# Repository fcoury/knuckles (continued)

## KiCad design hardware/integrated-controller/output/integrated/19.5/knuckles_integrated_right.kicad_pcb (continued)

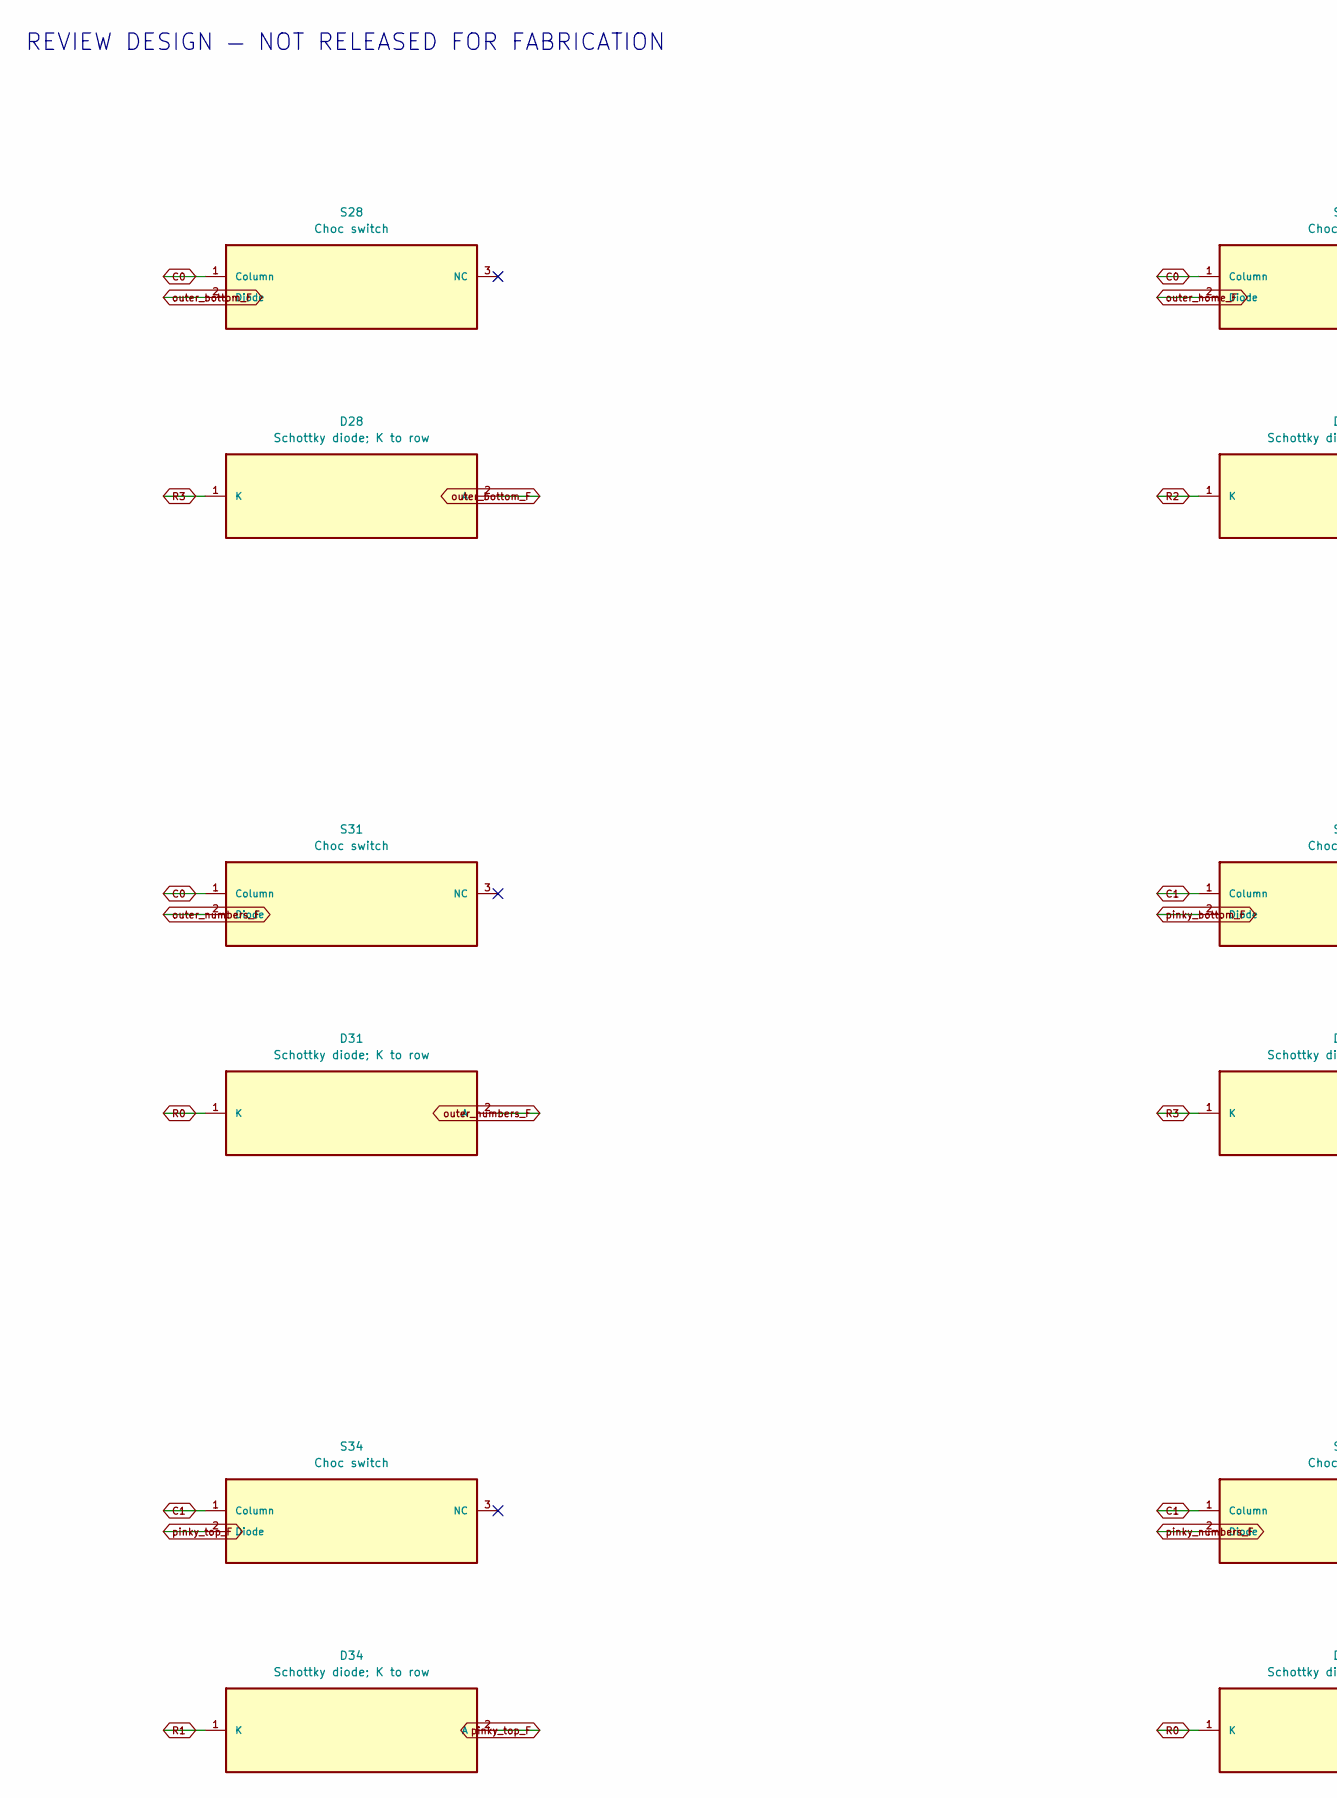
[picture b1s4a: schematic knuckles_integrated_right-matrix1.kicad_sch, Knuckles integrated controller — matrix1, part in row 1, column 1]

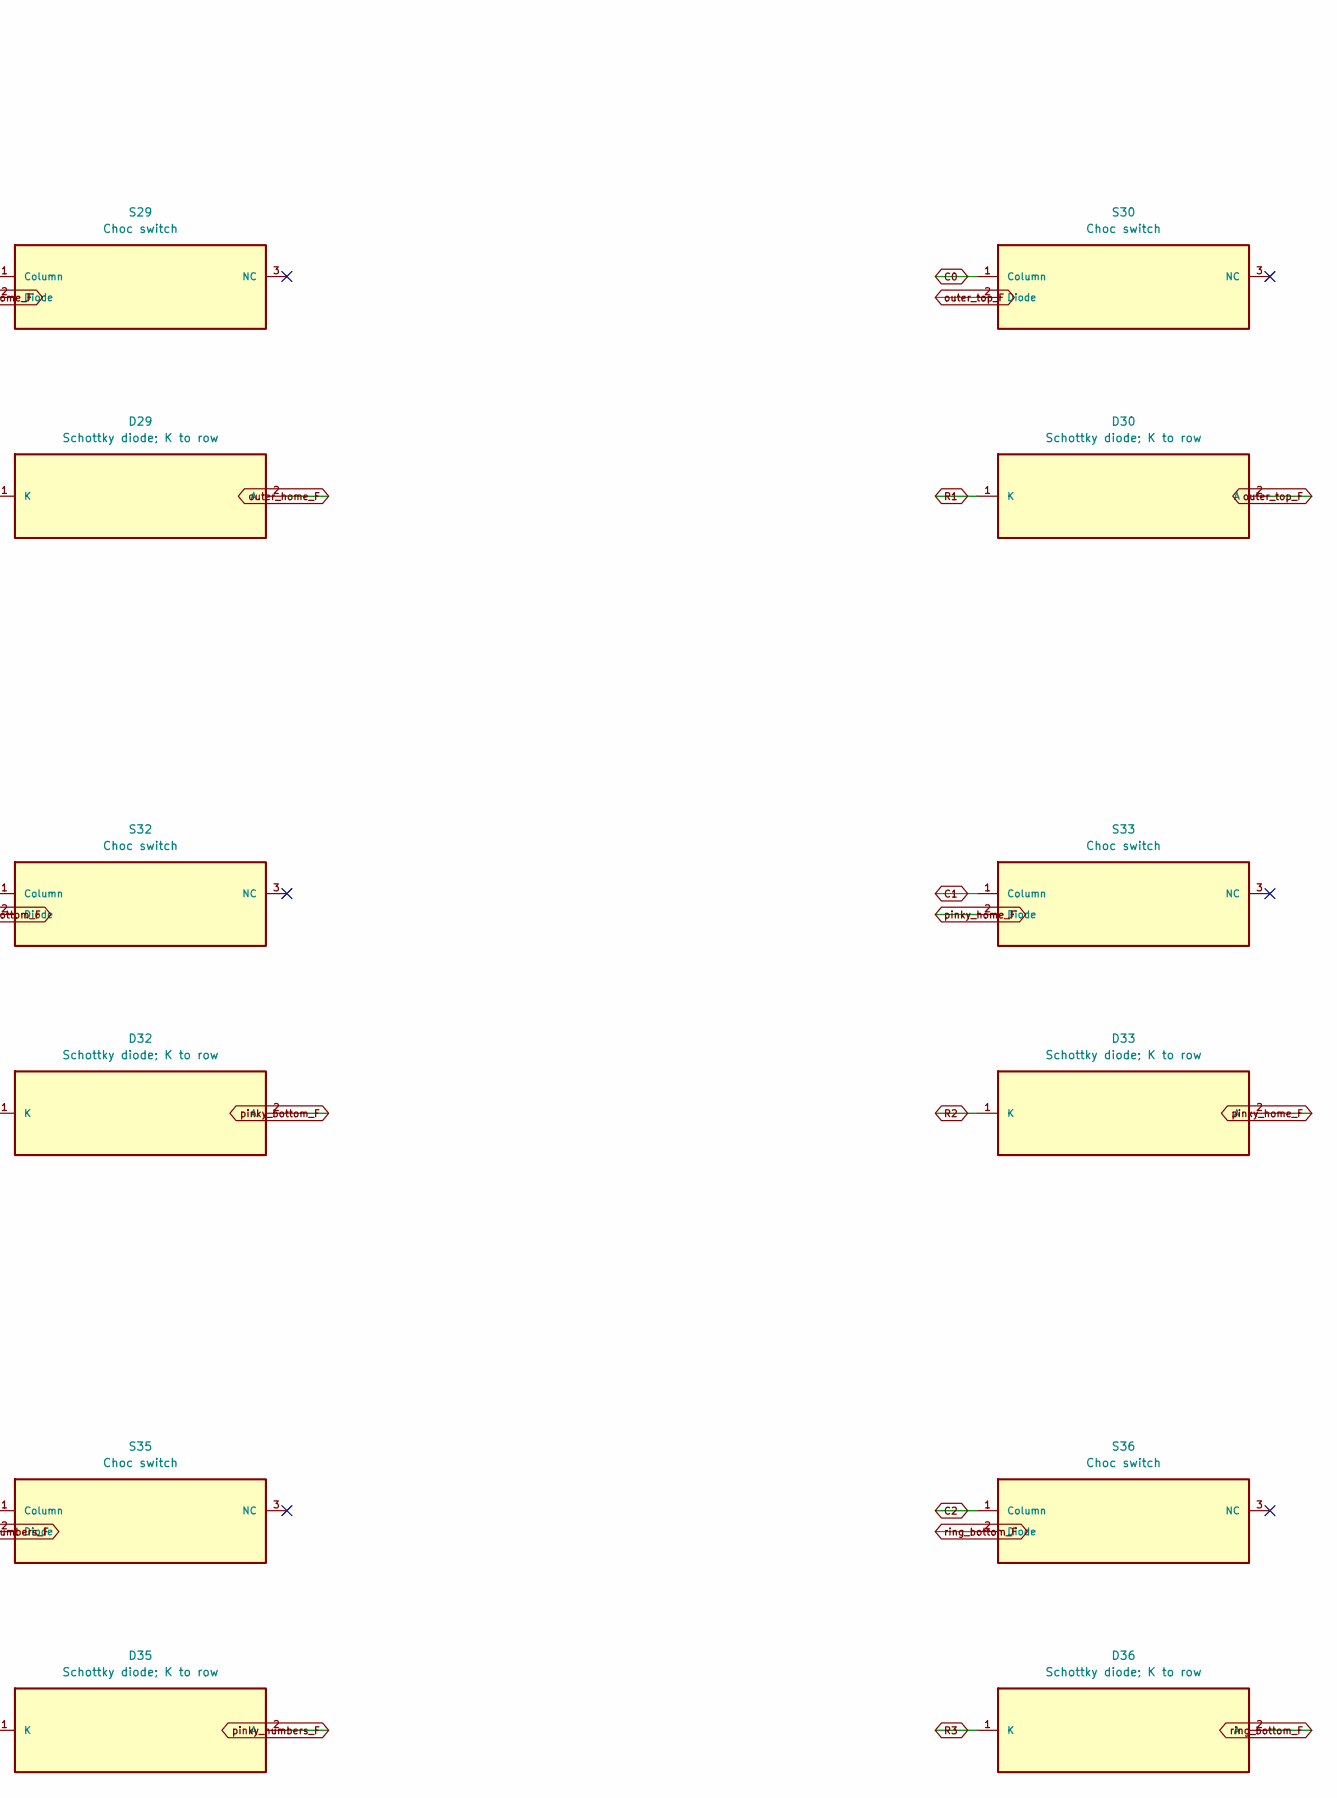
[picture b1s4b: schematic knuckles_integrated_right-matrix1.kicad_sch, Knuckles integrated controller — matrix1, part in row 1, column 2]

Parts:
D28, D29, D30, D31, D32, D33, D34, D35, D36: Schottky diode; K to row; diode_tht_sod123
S28, S29, S30, S31, S32, S33, S34, S35, S36: Choc switch; CPG1316S01D02

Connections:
C0: S28.1 (Column), S29.1 (Column), S30.1 (Column), S31.1 (Column); also elsewhere on the board
C1: S32.1 (Column), S33.1 (Column), S34.1 (Column), S35.1 (Column); also elsewhere on the board
C2: S36.1 (Column); also elsewhere on the board
R0: D31.1 (K), D35.1 (K); also elsewhere on the board
R1: D30.1 (K), D34.1 (K); also elsewhere on the board
R2: D29.1 (K), D33.1 (K); also elsewhere on the board
R3: D28.1 (K), D32.1 (K), D36.1 (K); also elsewhere on the board
outer_bottom_F: D28.2 (A), S28.2 (Diode)
outer_home_F: D29.2 (A), S29.2 (Diode)
outer_numbers_F: D31.2 (A), S31.2 (Diode)
outer_top_F: D30.2 (A), S30.2 (Diode)
pinky_bottom_F: D32.2 (A), S32.2 (Diode)
pinky_home_F: D33.2 (A), S33.2 (Diode)
pinky_numbers_F: D35.2 (A), S35.2 (Diode)
pinky_top_F: D34.2 (A), S34.2 (Diode)
ring_bottom_F: D36.2 (A), S36.2 (Diode)

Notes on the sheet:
REVIEW DESIGN — NOT RELEASED FOR FABRICATION

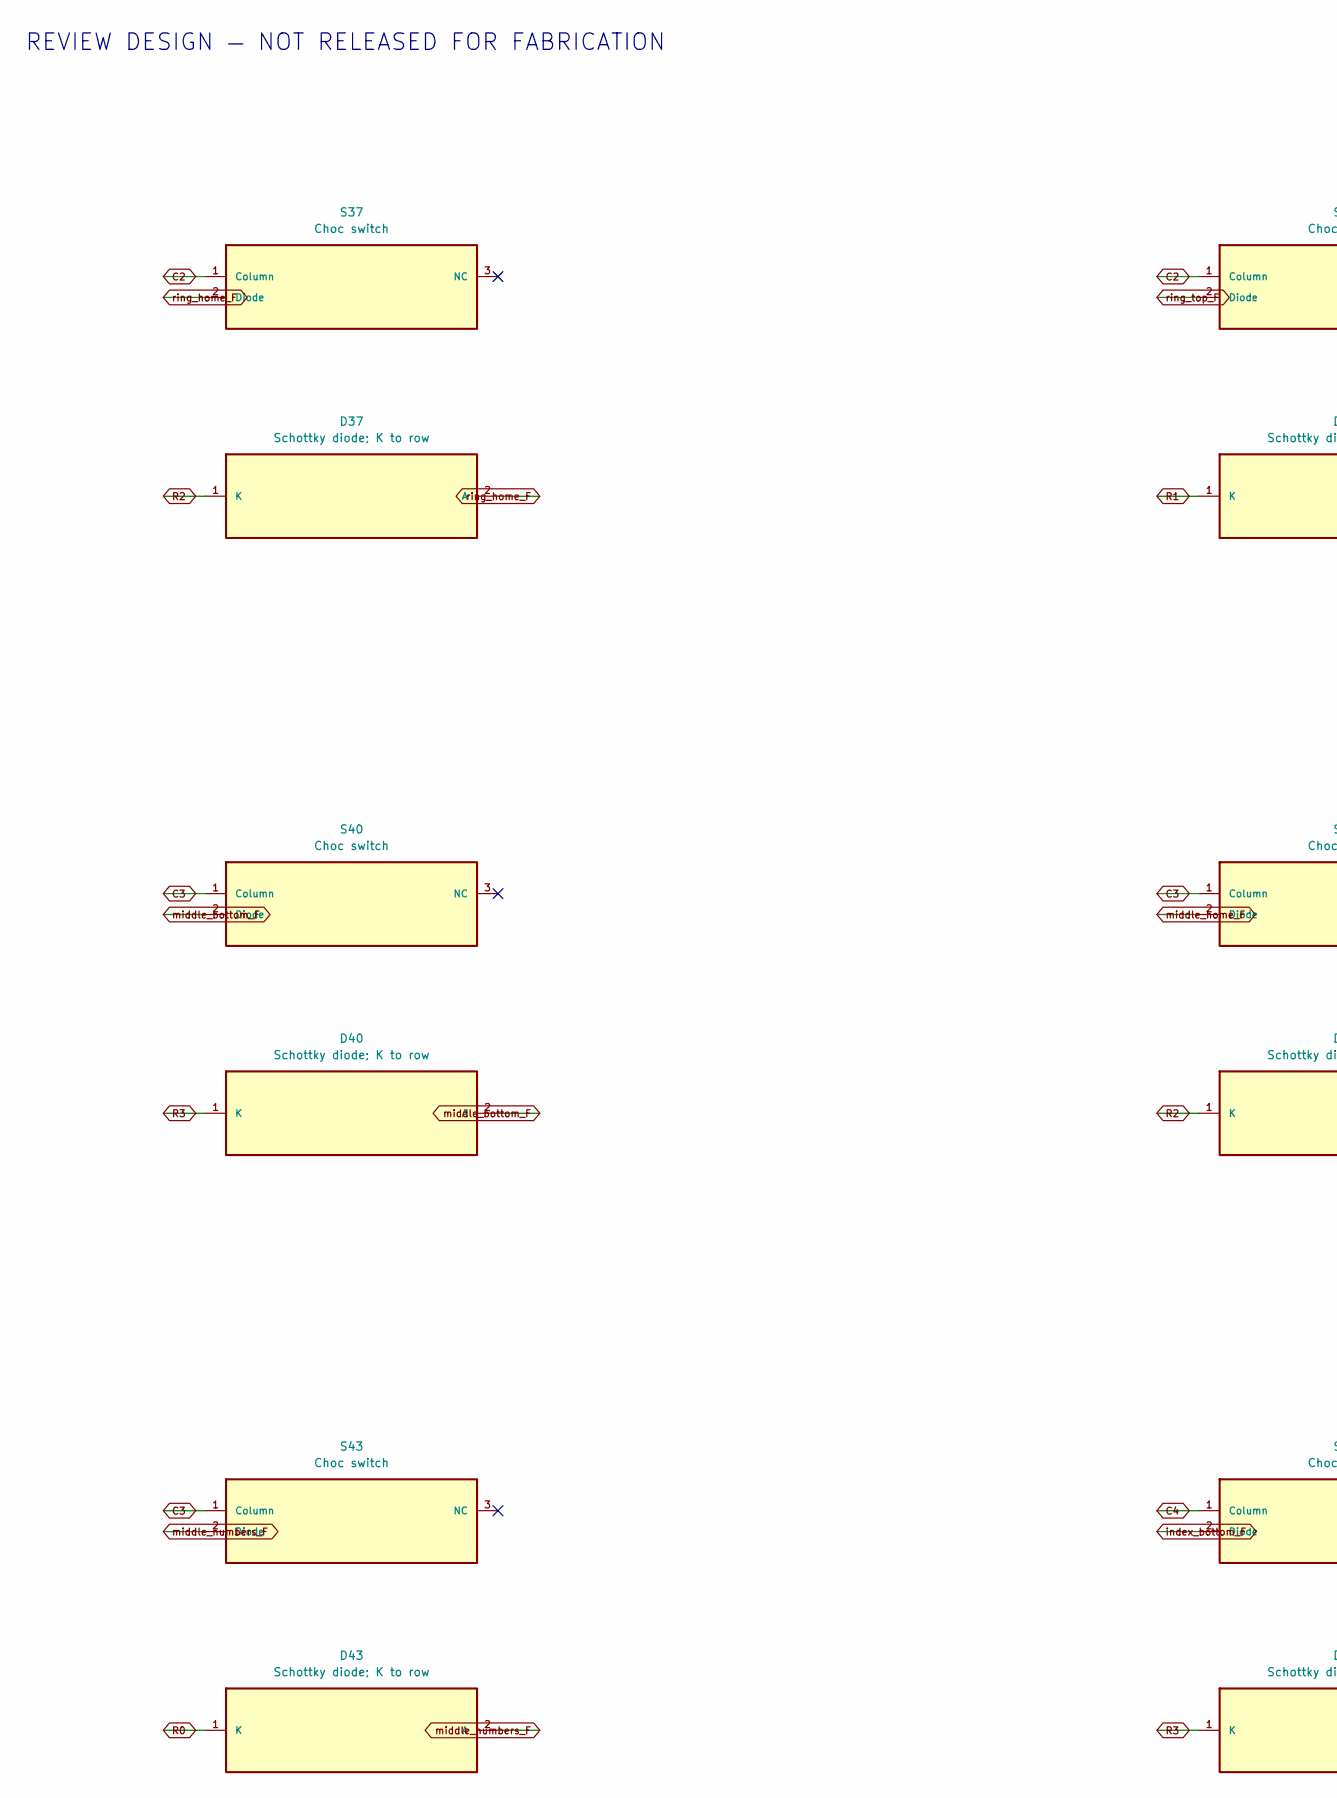
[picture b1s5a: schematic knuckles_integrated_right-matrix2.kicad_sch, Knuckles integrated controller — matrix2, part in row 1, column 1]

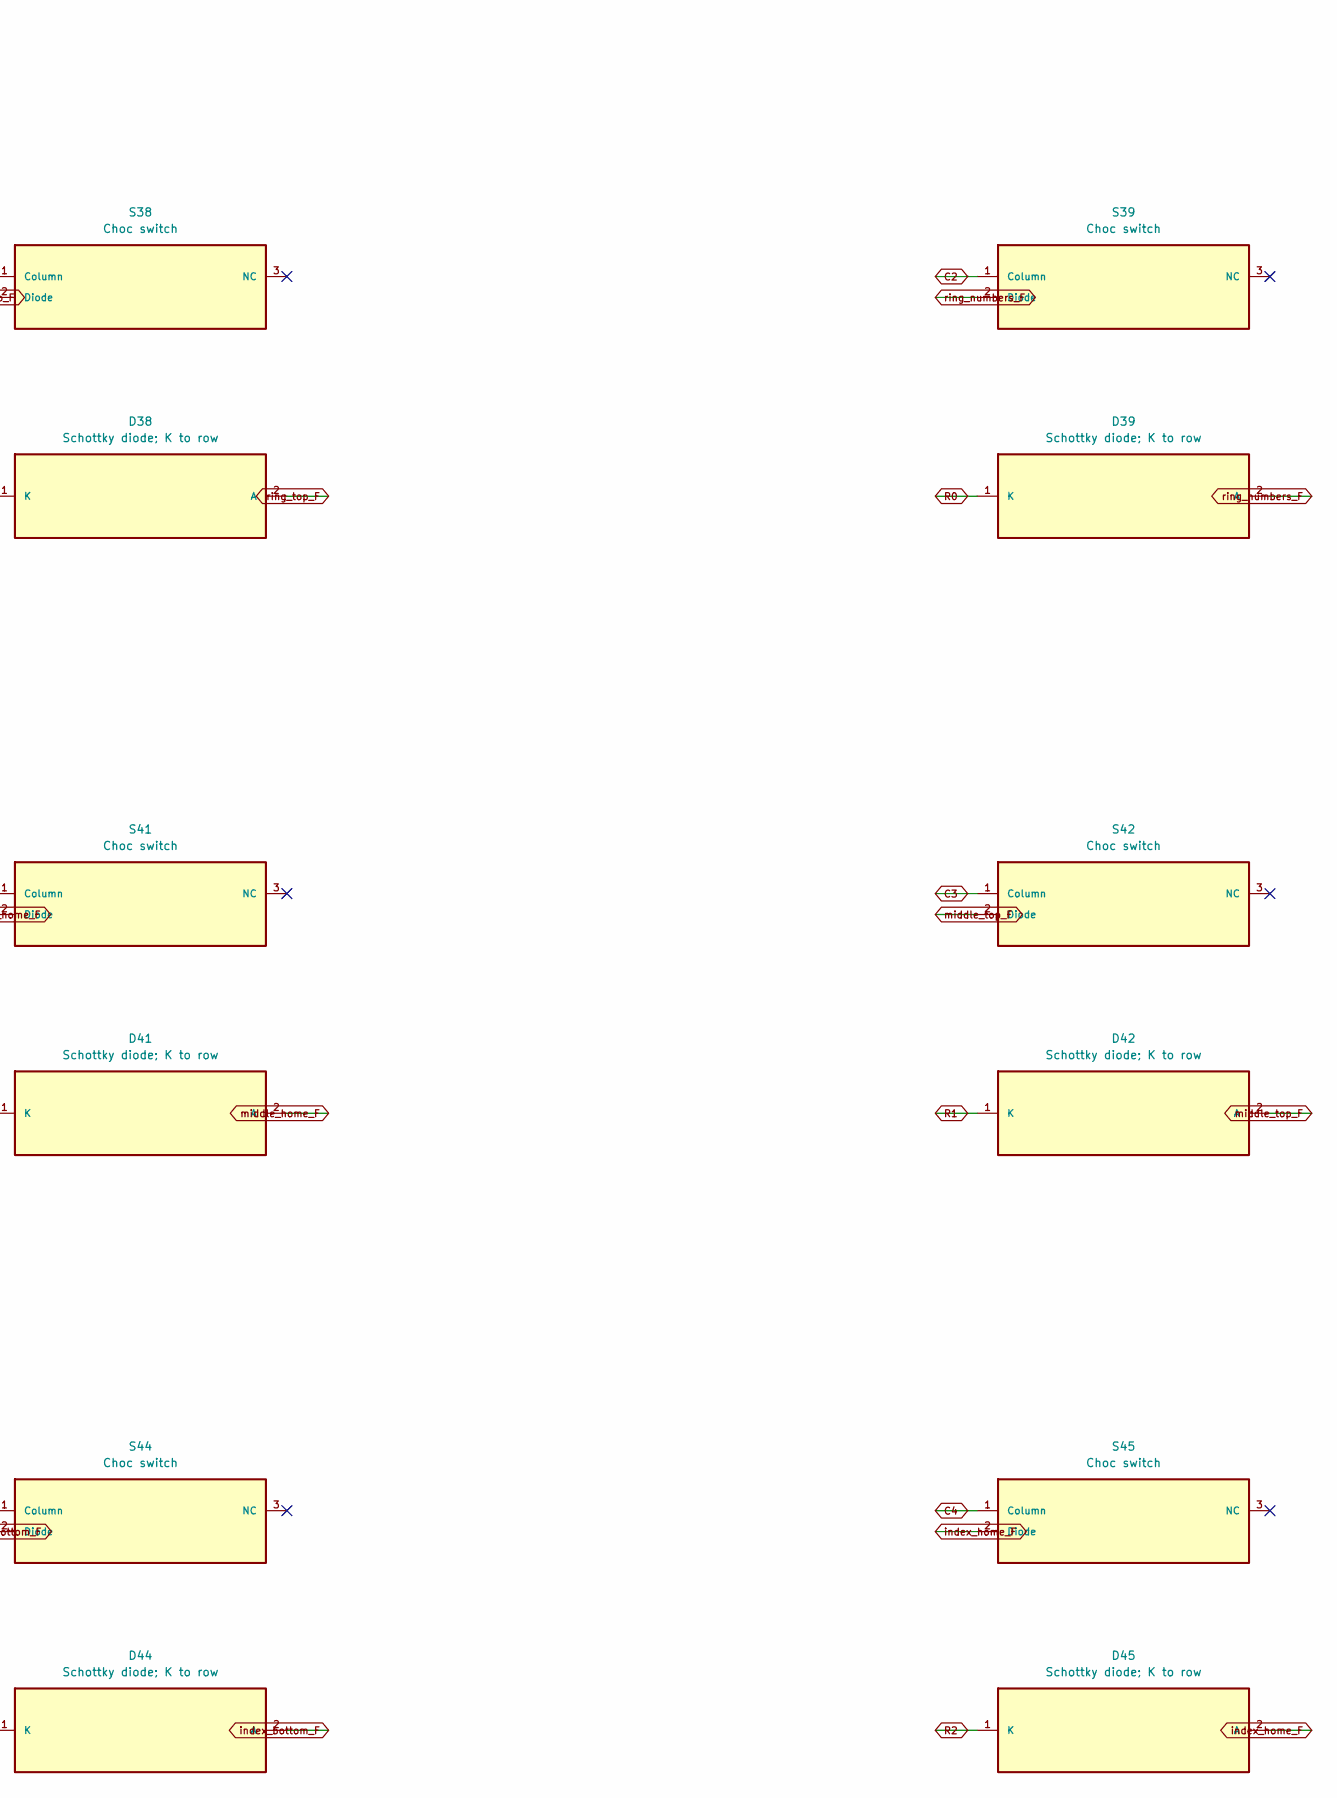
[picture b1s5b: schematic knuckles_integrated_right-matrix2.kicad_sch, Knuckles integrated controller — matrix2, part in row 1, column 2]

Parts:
D37, D38, D39, D40, D41, D42, D43, D44, D45: Schottky diode; K to row; diode_tht_sod123
S37, S38, S39, S40, S41, S42, S43, S44, S45: Choc switch; CPG1316S01D02

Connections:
C2: S37.1 (Column), S38.1 (Column), S39.1 (Column); also elsewhere on the board
C3: S40.1 (Column), S41.1 (Column), S42.1 (Column), S43.1 (Column); also elsewhere on the board
C4: S44.1 (Column), S45.1 (Column); also elsewhere on the board
R0: D39.1 (K), D43.1 (K); also elsewhere on the board
R1: D38.1 (K), D42.1 (K); also elsewhere on the board
R2: D37.1 (K), D41.1 (K), D45.1 (K); also elsewhere on the board
R3: D40.1 (K), D44.1 (K); also elsewhere on the board
index_bottom_F: D44.2 (A), S44.2 (Diode)
index_home_F: D45.2 (A), S45.2 (Diode)
middle_bottom_F: D40.2 (A), S40.2 (Diode)
middle_home_F: D41.2 (A), S41.2 (Diode)
middle_numbers_F: D43.2 (A), S43.2 (Diode)
middle_top_F: D42.2 (A), S42.2 (Diode)
ring_home_F: D37.2 (A), S37.2 (Diode)
ring_numbers_F: D39.2 (A), S39.2 (Diode)
ring_top_F: D38.2 (A), S38.2 (Diode)

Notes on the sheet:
REVIEW DESIGN — NOT RELEASED FOR FABRICATION

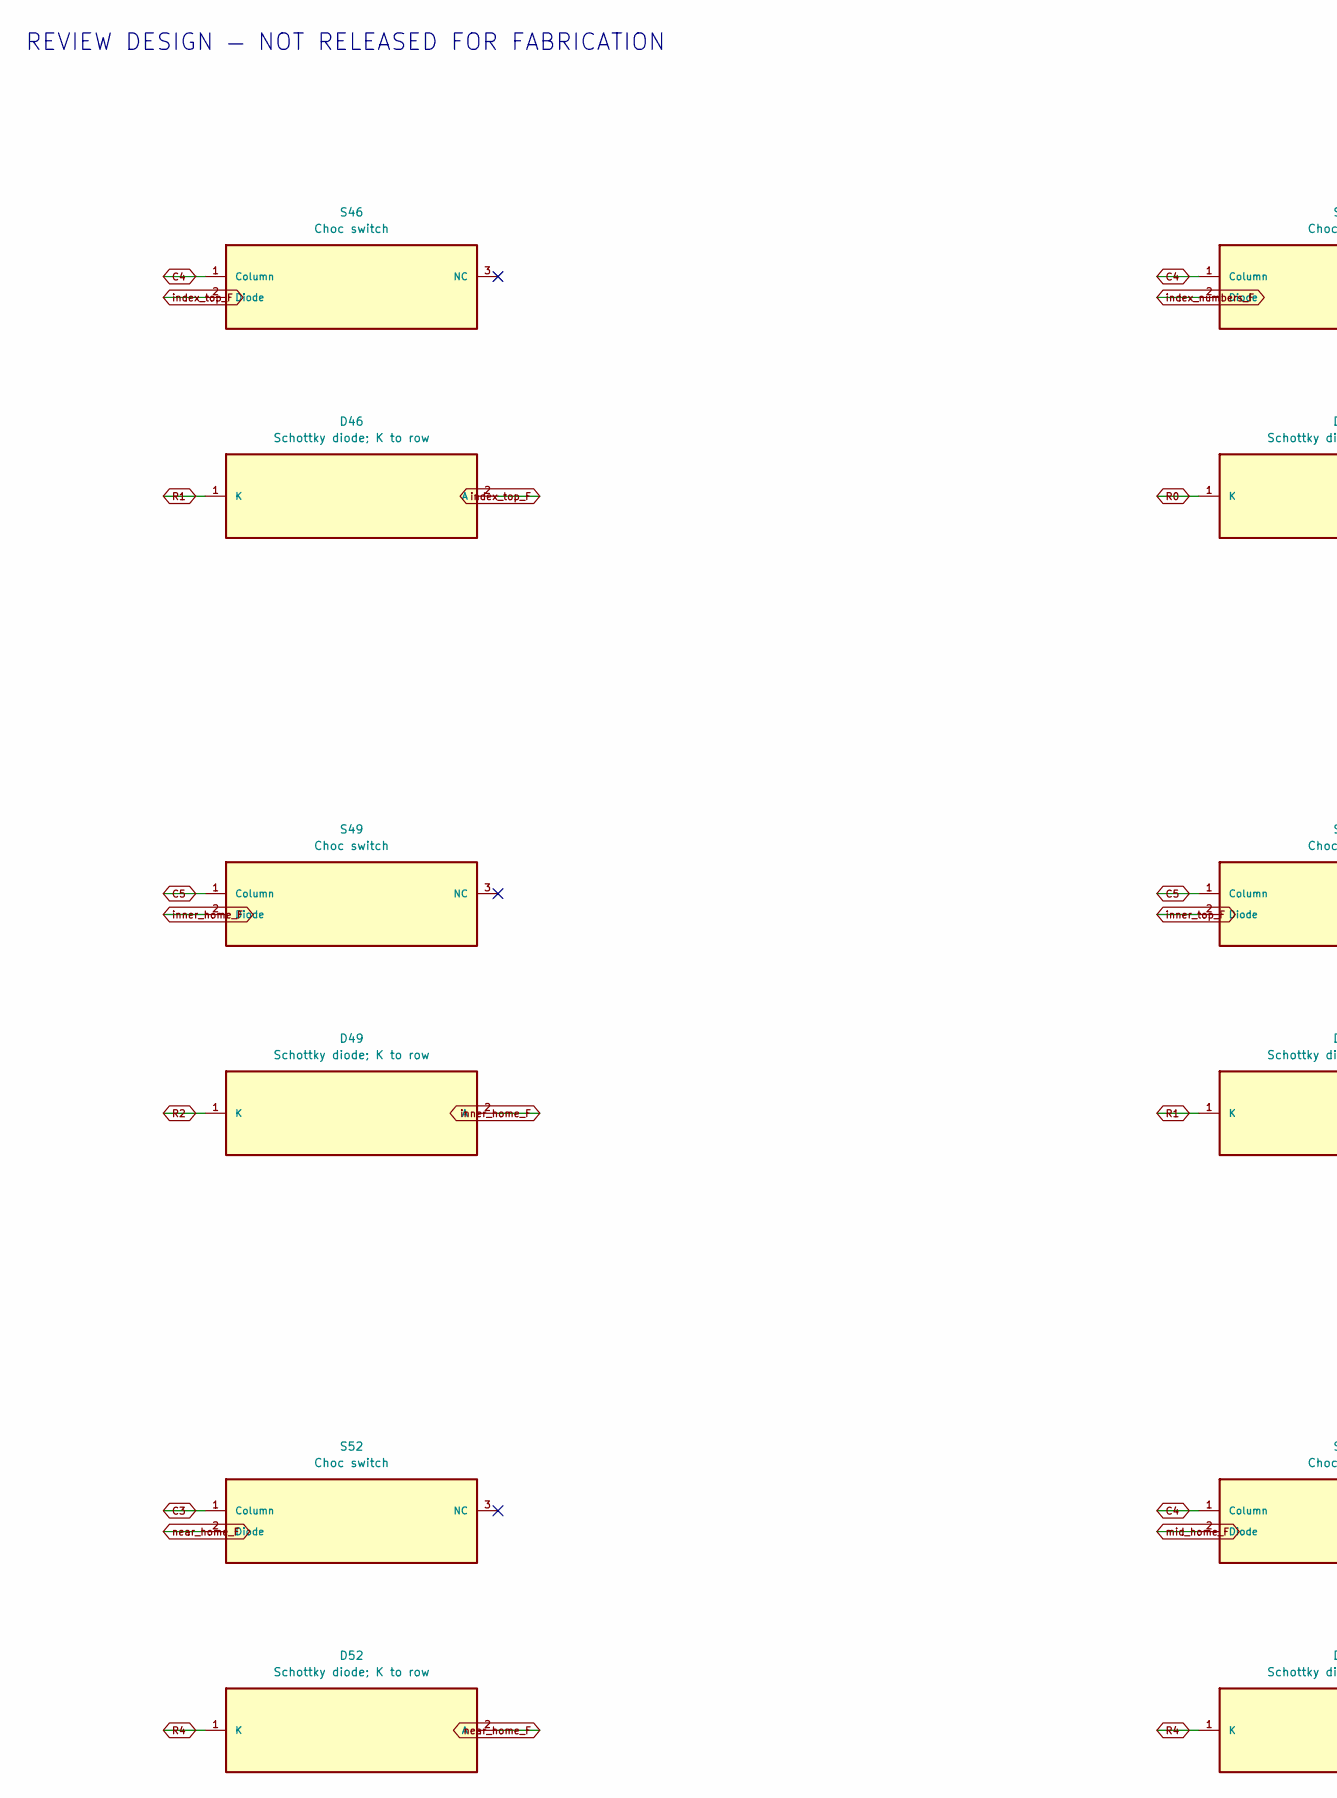
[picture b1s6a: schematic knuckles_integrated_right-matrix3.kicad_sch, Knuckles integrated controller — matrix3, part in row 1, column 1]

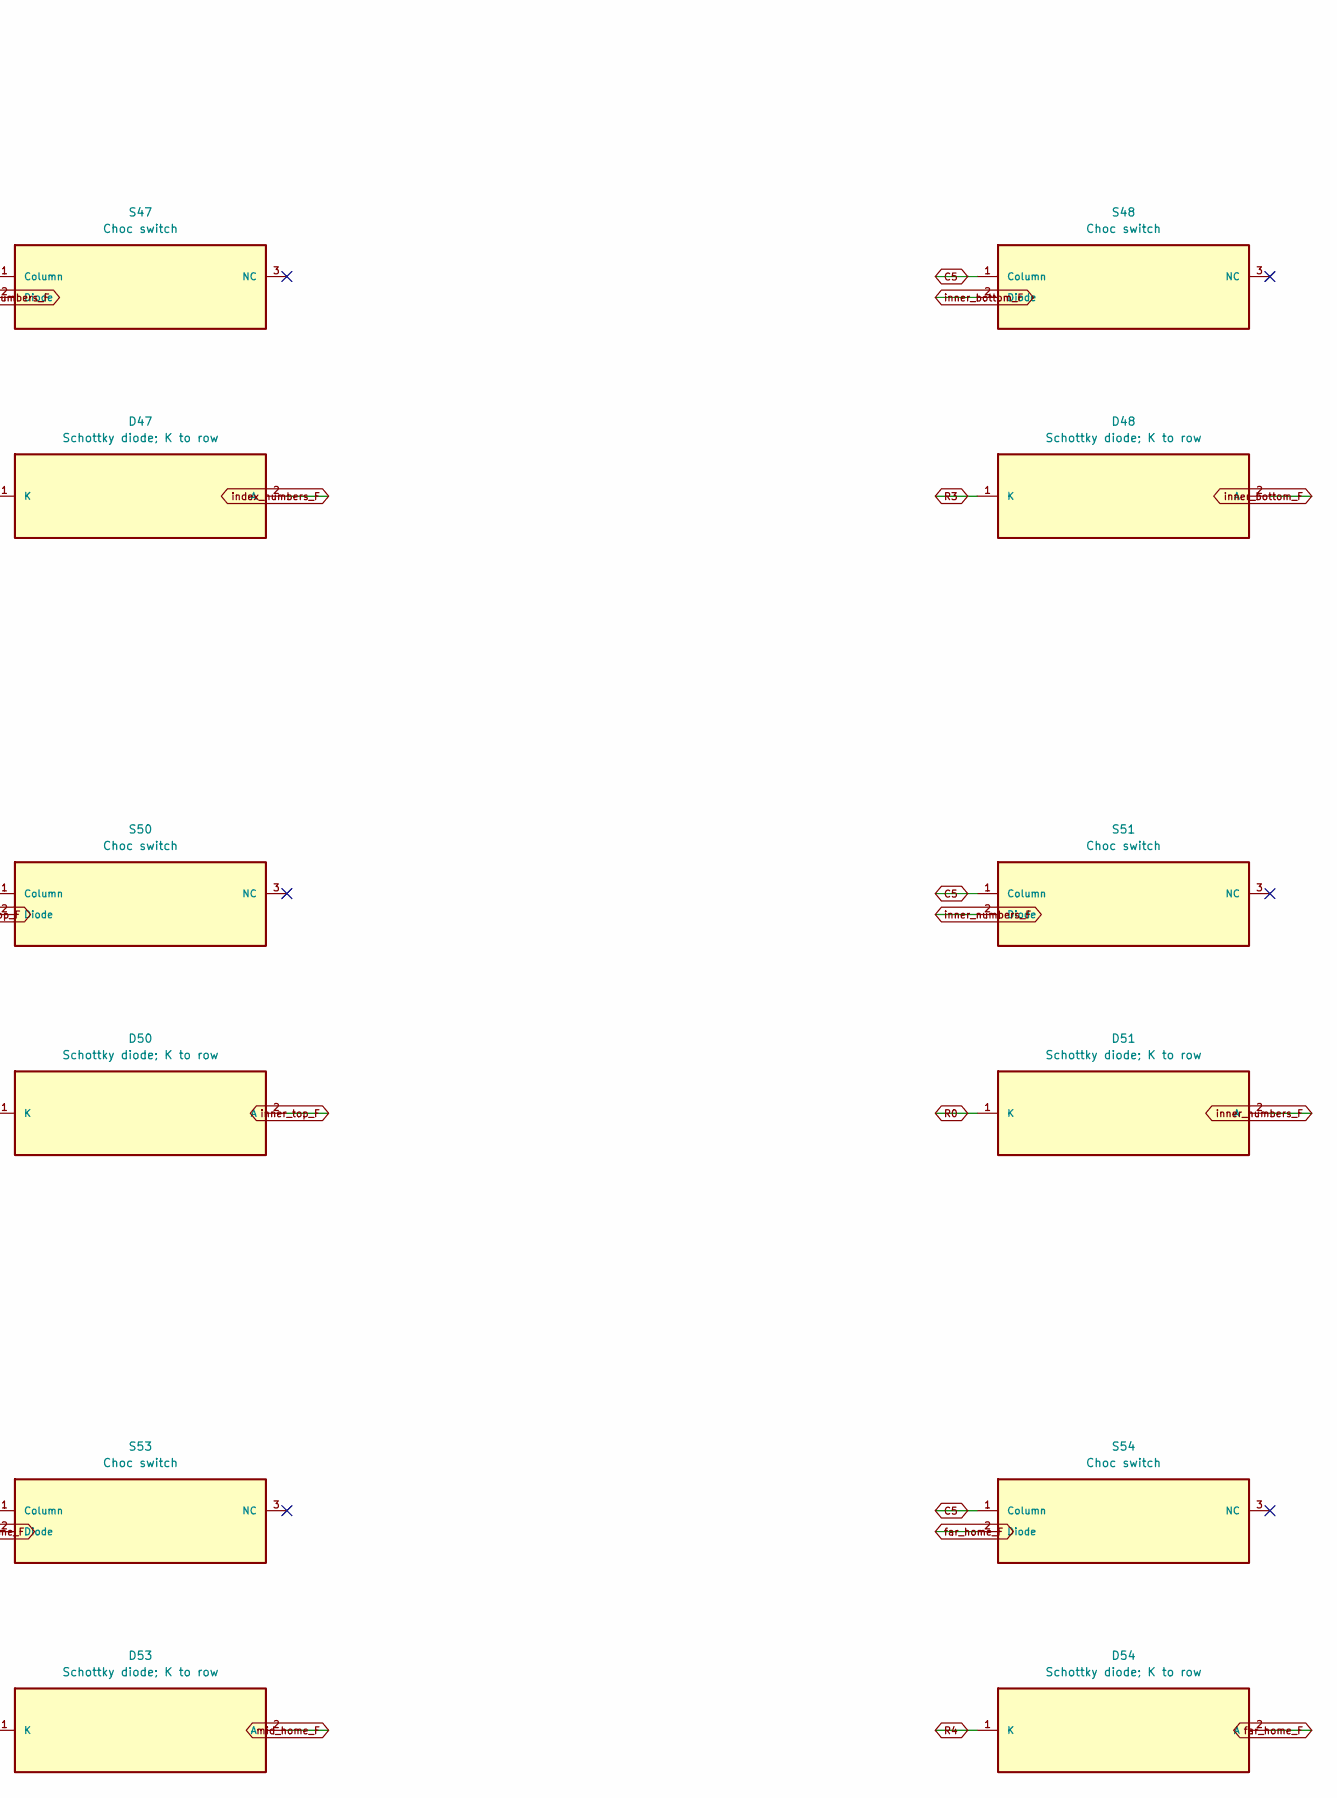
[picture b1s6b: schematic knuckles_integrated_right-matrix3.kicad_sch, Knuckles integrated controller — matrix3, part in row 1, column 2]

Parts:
D46, D47, D48, D49, D50, D51, D52, D53, D54: Schottky diode; K to row; diode_tht_sod123
S46, S47, S48, S49, S50, S51, S52, S53, S54: Choc switch; CPG1316S01D02

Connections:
C3: S52.1 (Column); also elsewhere on the board
C4: S46.1 (Column), S47.1 (Column), S53.1 (Column); also elsewhere on the board
C5: S48.1 (Column), S49.1 (Column), S50.1 (Column), S51.1 (Column), S54.1 (Column); also elsewhere on the board
R0: D47.1 (K), D51.1 (K); also elsewhere on the board
R1: D46.1 (K), D50.1 (K); also elsewhere on the board
R2: D49.1 (K); also elsewhere on the board
R3: D48.1 (K); also elsewhere on the board
R4: D52.1 (K), D53.1 (K), D54.1 (K); also elsewhere on the board
far_home_F: D54.2 (A), S54.2 (Diode)
index_numbers_F: D47.2 (A), S47.2 (Diode)
index_top_F: D46.2 (A), S46.2 (Diode)
inner_bottom_F: D48.2 (A), S48.2 (Diode)
inner_home_F: D49.2 (A), S49.2 (Diode)
inner_numbers_F: D51.2 (A), S51.2 (Diode)
inner_top_F: D50.2 (A), S50.2 (Diode)
mid_home_F: D53.2 (A), S53.2 (Diode)
near_home_F: D52.2 (A), S52.2 (Diode)

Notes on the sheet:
REVIEW DESIGN — NOT RELEASED FOR FABRICATION

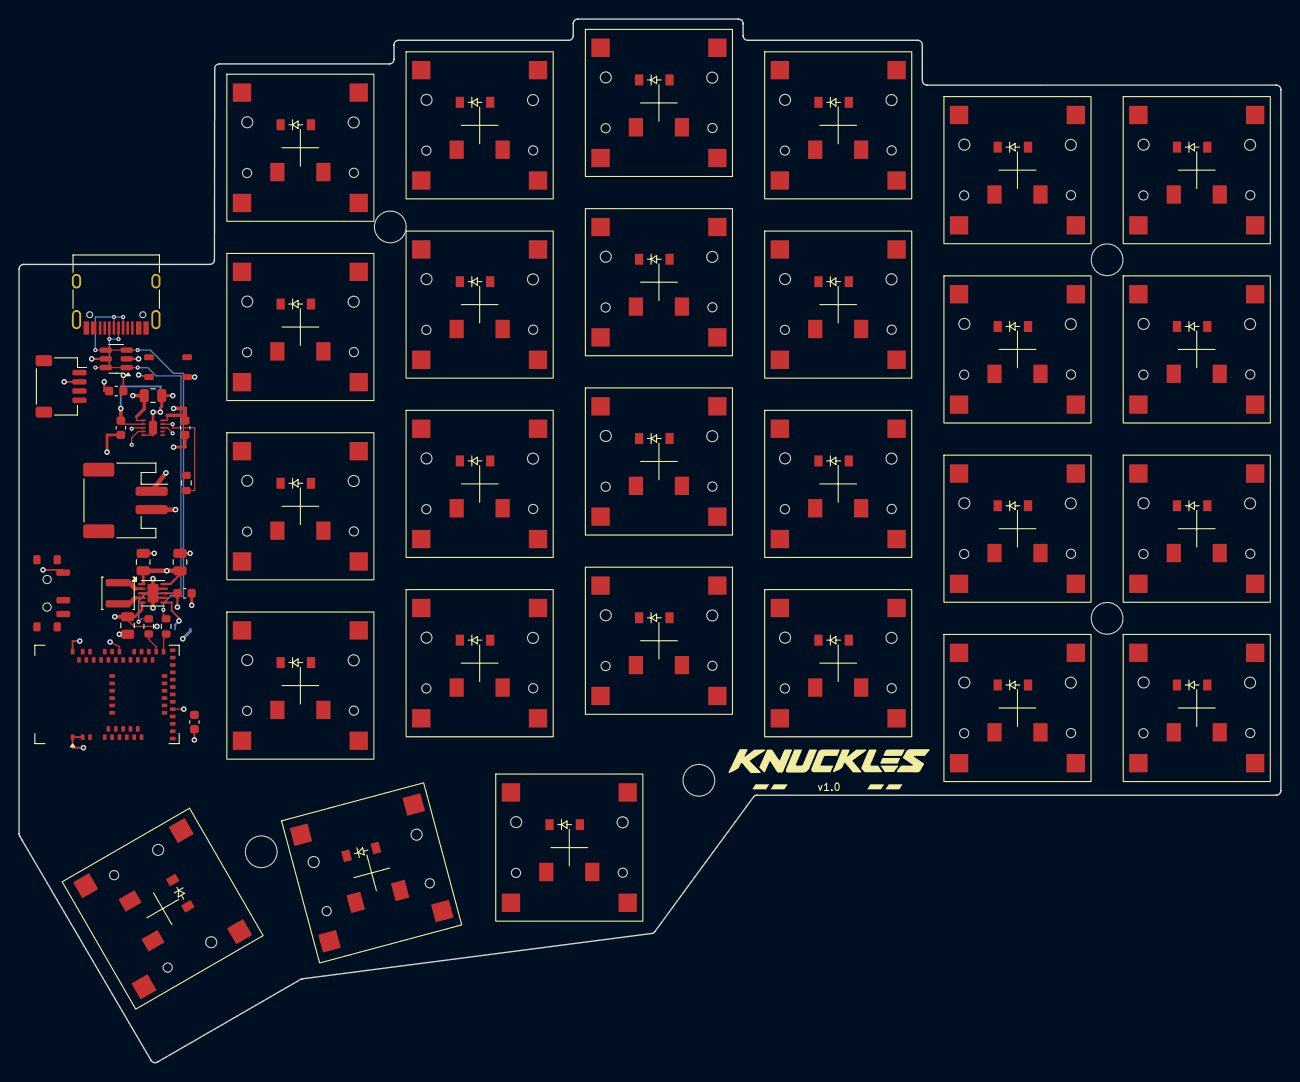
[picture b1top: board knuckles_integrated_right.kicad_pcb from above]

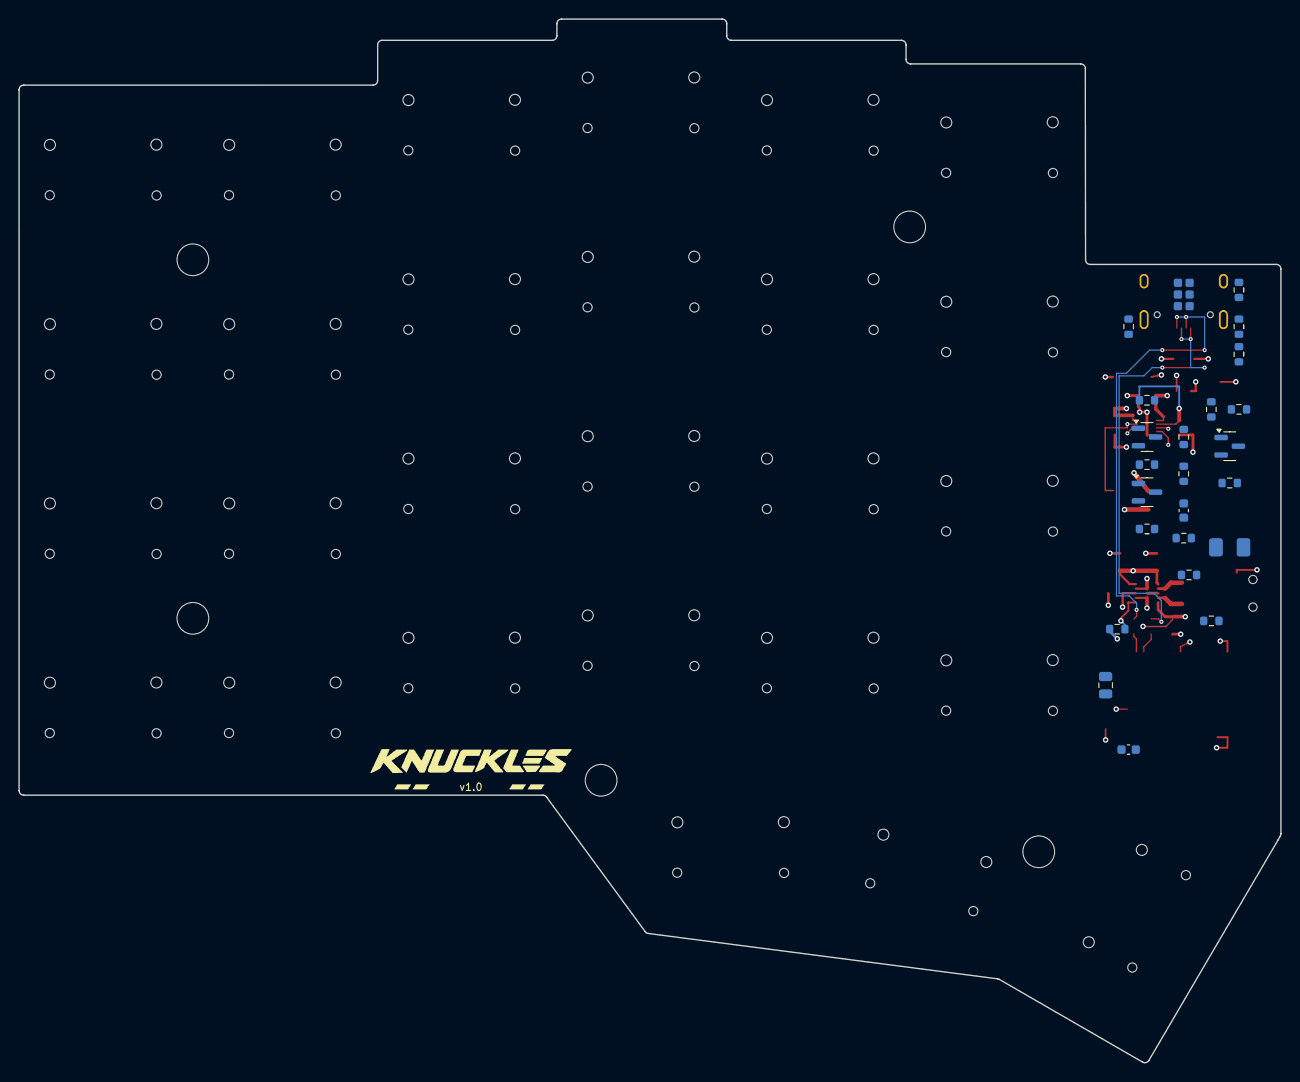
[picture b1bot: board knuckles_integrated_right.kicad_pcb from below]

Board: 4 copper layers, 137.3 x 113.5 mm, 106 parts (24 on the bottom side), 69 nets.

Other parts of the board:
ART2: knuckles_artwork_wordmark
MH3, MH4, MH5, MH6, MH7: mounting_hole_npth

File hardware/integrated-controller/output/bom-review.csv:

Designator,Value,Footprint,LCSC Part #,Populate,Catalog MPN,Catalog stock snapshot,Notes
U1,MDBT50Q-1MV2,Raytac_MDBT50Q,C5118826,yes,MDBT50Q-1MV2,0,Normal-voltage mode: VDD and VDDH tied to 3.3V; DCCH NC; LF clock uses calibrated internal RC. JLC stock zero at sourcing snapshot.
J1,TYPE-C-31-M-12,USB_C_Receptacle_HRO_TYPE-C-31-M-12,C165948,yes,TYPE-C-31-M-12,364676,
U4,USBLC6-2SC6,SOT-23-6,C7519,yes,USBLC6-2SC6,34266,
R1,5.1k,R_0603_1608Metric,C23186,yes,0603WAF5101T5E,23514694,
R2,5.1k,R_0603_1608Metric,C23186,yes,0603WAF5101T5E,23514694,
J2,S2B-PH-SM4-TB(LF)(SN),JST_PH_S2B-PH-SM4-TB_1x02-1MP_P2.00mm_Horizontal,C295747,yes,S2B-PH-SM4-TB(LF)(SN),36001,Protected 1S LiPo only. Verify actual cable polarity; capacity is not a voltage rating.
J3,SM04B-SRSS-TB(LF)(SN),JST_SH_SM04B-SRSS-TB_1x04-1MP_P1.00mm_Horizontal,C160404,yes,SM04B-SRSS-TB(LF)(SN),60361,New custom cable to existing TPS43 adapter; connector is not the raw sensor FPC pinout.
J4,Matrix bring-up header,PinHeader_1x12_P2.54mm_Vertical,,DNP,,unknown,"Bench connector, manually fitted; replaced by matrix traces in keyboard integration."
J5,SWD pogo interface,SWD_2x3_P1.27_NoHoles,,DNP,,unknown,"Six bare pads on 1.27mm pitch; custom pogo fixture, not a mechanically compatible Tag-Connect connector. Pin 1 is target voltage sense, not external power input."
SW1,SSSS811101,SSSS811101,C109335,yes,SSSS811101,37397,ALPS SSSS811101; pad dimensions checked against manufacturer mounting drawing.
SW2,SKRPANE010,SKRPANE010,C470426,yes,SKRPANE010,11804,
R3,10k,R_0603_1608Metric,C25804,yes,0603WAF1002T5E,31137295,
R4,4.7k,R_0603_1608Metric,C23162,DNP,0603WAF4701T5E,18641065,Fit only if the attached TPS43 adapter lacks pull-ups; confirm effective parallel pull-up resistance.
R5,4.7k,R_0603_1608Metric,C23162,DNP,0603WAF4701T5E,18641065,Fit only if the attached TPS43 adapter lacks pull-ups; confirm effective parallel pull-up resistance.
R6,10k,R_0603_1608Metric,C25804,yes,0603WAF1002T5E,31137295,
R7,10k,R_0603_1608Metric,C25804,yes,0603WAF1002T5E,31137295,
C1,100nF,C_0603_1608Metric,C14663,yes,CC0603KRX7R9BB104,31872643,
C2,22uF,C_0805_2012Metric,C45783,yes,CL21A226MAQNNNE,3768424,
C3,4.7uF,C_0603_1608Metric,C19666,yes,CL10A475KO8NNNC,3534195,
U2,BQ25186DLHR,TI_WSON_DLH0010A,C44639442,yes,BQ25186DLHR,264,I2C 0x6A on dedicated bus. CE held disabled until firmware verifies profile and USB state; R12 assembly interlock.
U3,TPS63031DSKR,WSON-10-1EP_2.5x2.5mm_P0.5mm_EP1.2x2mm,C15516,yes,TPS63031DSKR,5172,
L1,1.5uH SWPA3015S1R5NT,L_Sunlord_SWPA3015S,C56594,yes,SWPA3015S1R5NT,3825,"Published NT variant: 1.5uH +/-30%, 2.30A saturation, 1.70A thermal rating. See Sunlord table and sourcing review."
R8,10k,R_0603_1608Metric,C25804,yes,0603WAF1002T5E,31137295,Dedicated PMIC bus pull-up; independent of external TPS43 pull-ups.
R9,10k,R_0603_1608Metric,C25804,yes,0603WAF1002T5E,31137295,Dedicated PMIC bus pull-up.
R10,100k,R_0603_1608Metric,C25803,yes,0603WAF1003T5E,19364156,Hardware defaults to disabled charging while MCU is off/reset.
R11,100k,R_0603_1608Metric,C25803,yes,0603WAF1003T5E,19364156,VBUS-domain CE pull-up. Q3 isolates the MCU GPIO from 5V.
R12,0R,R_0603_1608Metric,C21189,DNP,0603WAF0000T5E,23652384,Assembly charge interlock; fit after selected cell/NTC and firmware validation. Does not bypass firmware control.
R13,1M,R_0603_1608Metric,C22935,yes,0603WAF1004T5E,5464881,Keep the regulator disabled while the mechanical switch is between contacts.
C4,2.2uF,C_0603_1608Metric,C23630,yes,,unknown,
C5,2.2uF,C_0603_1608Metric,C23630,yes,,unknown,
C6,22uF,C_0805_2012Metric,C45783,yes,CL21A226MAQNNNE,3768424,
C8,22uF,C_0805_2012Metric,C45783,yes,CL21A226MAQNNNE,3768424,
C9,100nF,C_0603_1608Metric,C14663,yes,CC0603KRX7R9BB104,31872643,
C10,22uF,C_0805_2012Metric,C45783,yes,CL21A226MAQNNNE,3768424,
C11,22uF,C_0805_2012Metric,C45783,yes,CL21A226MAQNNNE,3768424,
J6,External 10k NTC pads,NTC_WirePads,,DNP,,unknown,"Attach an insulated external 10k NTC, beta 3435K, thermally coupled to the cell before enabling charging. Not simulated with a fixed resistor."
Q1,AO3401A,SOT-23,C15127,yes,AO3401A,697471,
Q2,2N7002,SOT-23,C8545,yes,2N7002,2596656,
R14,1M,R_0603_1608Metric,C22935,yes,0603WAF1004T5E,5464881,
R15,10k,R_0603_1608Metric,C25804,yes,0603WAF1002T5E,31137295,
R16,10k,R_0603_1608Metric,C25804,yes,0603WAF1002T5E,31137295,
R17,1M,R_0603_1608Metric,C22935,yes,0603WAF1004T5E,5464881,
C12,100nF,C_0603_1608Metric,C14663,yes,CC0603KRX7R9BB104,31872643,
Q3,2N7002,SOT-23,C8545,yes,2N7002,2596656,
R18,27R,R_0603_1608Metric,C25190,yes,0603WAF270JT5E,232340,
R19,27R,R_0603_1608Metric,C25190,yes,0603WAF270JT5E,232340,
C13,100nF,C_0603_1608Metric,C14663,yes,CC0603KRX7R9BB104,31872643,
